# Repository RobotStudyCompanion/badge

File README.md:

# Tiny RSC Badge

This repository contains the PCB design files for the **Tiny RSC Badge**, developed for the Robotic Study Companion (RSC) project.

The board is a small electronic badge designed around an **astable multivibrator circuit** that drives blinking LEDs. The project was created as a simple and compact PCB badge for the RSC platform.

## Design Summary

The PCB was designed in **KiCad**.

The circuit is based on an astable multivibrator, where two transistor stages continuously switch between ON and OFF states, causing the LEDs to blink alternately.

The board includes:

- Astable multivibrator circuit
- Two LEDs
- Transistors
- Resistors and capacitors for controlling the oscillation
- Compact badge-style PCB layout

The design focuses on simplicity, low component count, and a compact form factor suitable for use as an electronic badge.

## PCB

### Front Side

### Back Side

## Final Product

The assembled Tiny RSC Badge:

---

## Author

Timur Kedrov and Matevž Borjan Zorec 

© Robot Study Companion 2026

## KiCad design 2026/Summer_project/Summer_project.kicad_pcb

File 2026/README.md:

# RSC Badge

This repository contains the PCB design files for the **RSC Badge**, developed for the Robot Study Companion (RSC; [rsc.ee](https://rsc.ee/)) project.

The board is a small electronic badge featuring an astable multivibrator circuit that drives blinking LEDs. 

For the circuit design we were explicitly inspired by the KiCad workshop at [https://gitlab.com/evils/kicad-workshop](https://gitlab.com/evils/kicad-workshop).

We prepared this project as a simple and compact PCB badge for RSC affiliated events.

## Design Summary

We designed the PCB in **KiCad 10.0**.

The astable multivibrator circuit comprises two transistor stages.

When pressing the button switch, the transistors alternate ON and OFF states, causing the LEDs to blink alternately, while the middle LED stays powered.

The board includes:
- Two LEDs
- Two transistors
- Button switch
- CR2032 battery holder
- Informative silkscreen
- Resistors and capacitors (current limiting and oscillation rate setting)
- Compact badge with a face-shape layout (pareidolia)

### Front

### Back

## Assembled 2026 RSC Badge:

---

## Author

Timur Kedrov and Matevž Borjan Zorec 

Supervised by Farnaz Baksh

© Robot Study Companion 2026

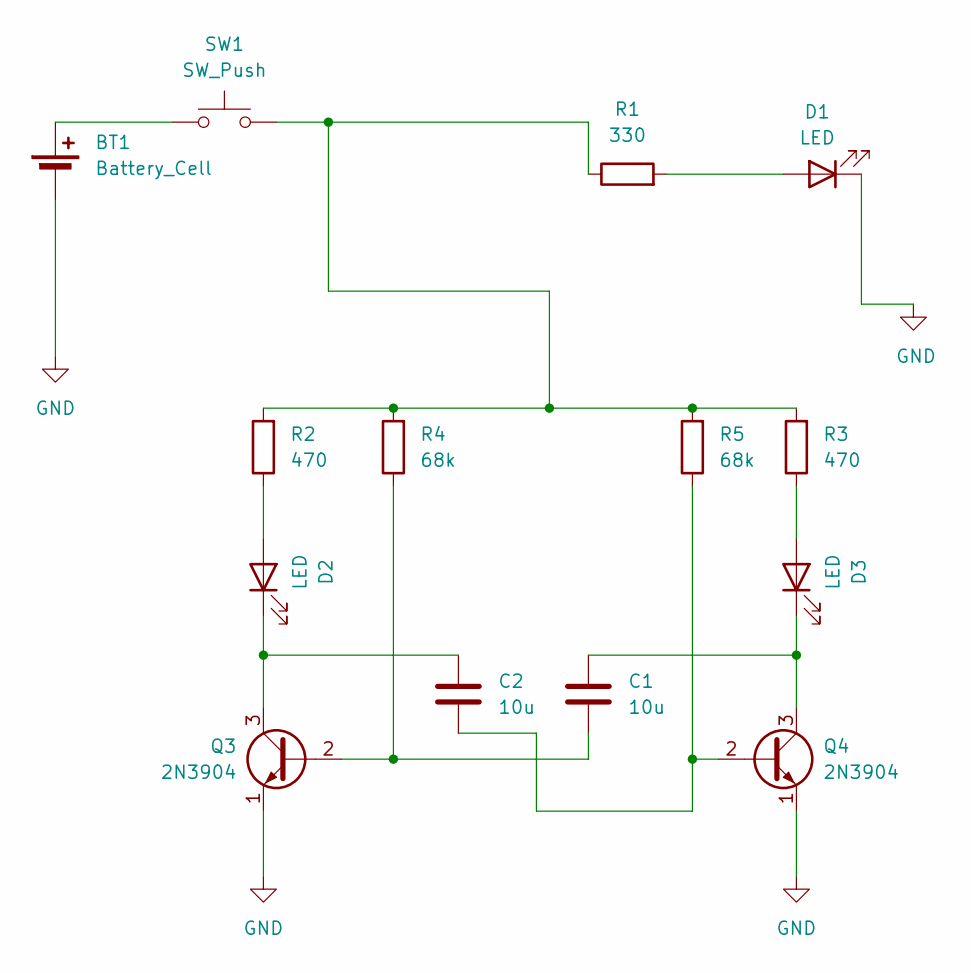
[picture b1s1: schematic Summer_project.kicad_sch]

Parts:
BT1: Battery_Cell; BAT_BAT-HLD-005-THM
C1, C2: 10u; CP_Radial_D5.0mm_P2.00mm
D1, D2, D3: LED; LED_D5.0mm
Q3, Q4: 2N3904; TO-92_Inline
R1: 330; R_Axial_DIN0207_L6.3mm_D2.5mm_P7.62mm_Horizontal
R2, R3: 470; R_Axial_DIN0207_L6.3mm_D2.5mm_P7.62mm_Horizontal
R4, R5: 68k; R_Axial_DIN0207_L6.3mm_D2.5mm_P7.62mm_Horizontal
SW1: SW_Push; SW_PUSH_6mm

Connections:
GND: BT1.2 (-), D1.1 (K), Q3.1 (E), Q4.1 (E)
unnamed: BT1.1 (+), SW1.1
unnamed: D1.2 (A), R1.2
unnamed: D2.2 (A), R2.1
unnamed: C2.1, D2.1 (K), Q3.3 (C)
unnamed: D3.2 (A), R3.1
unnamed: C1.1, D3.1 (K), Q4.3 (C)
unnamed: C1.2, Q3.2 (B), R4.1
unnamed: C2.2, Q4.2 (B), R5.1
unnamed: R1.1, R2.2, R3.2, R4.2, R5.2, SW1.2

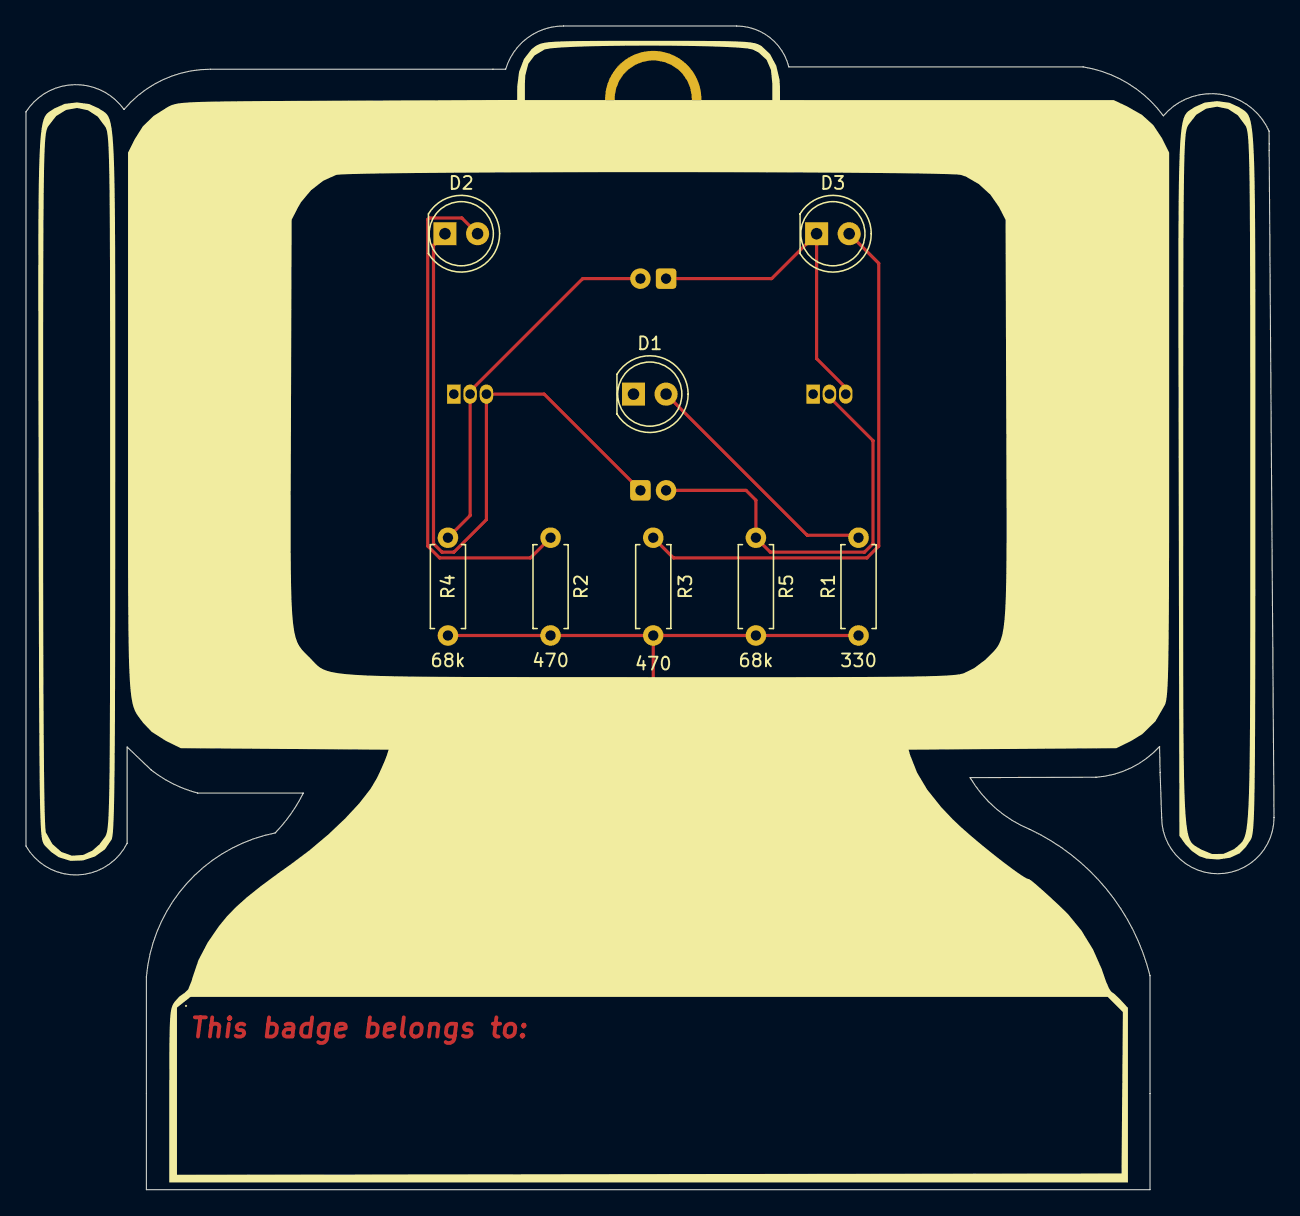
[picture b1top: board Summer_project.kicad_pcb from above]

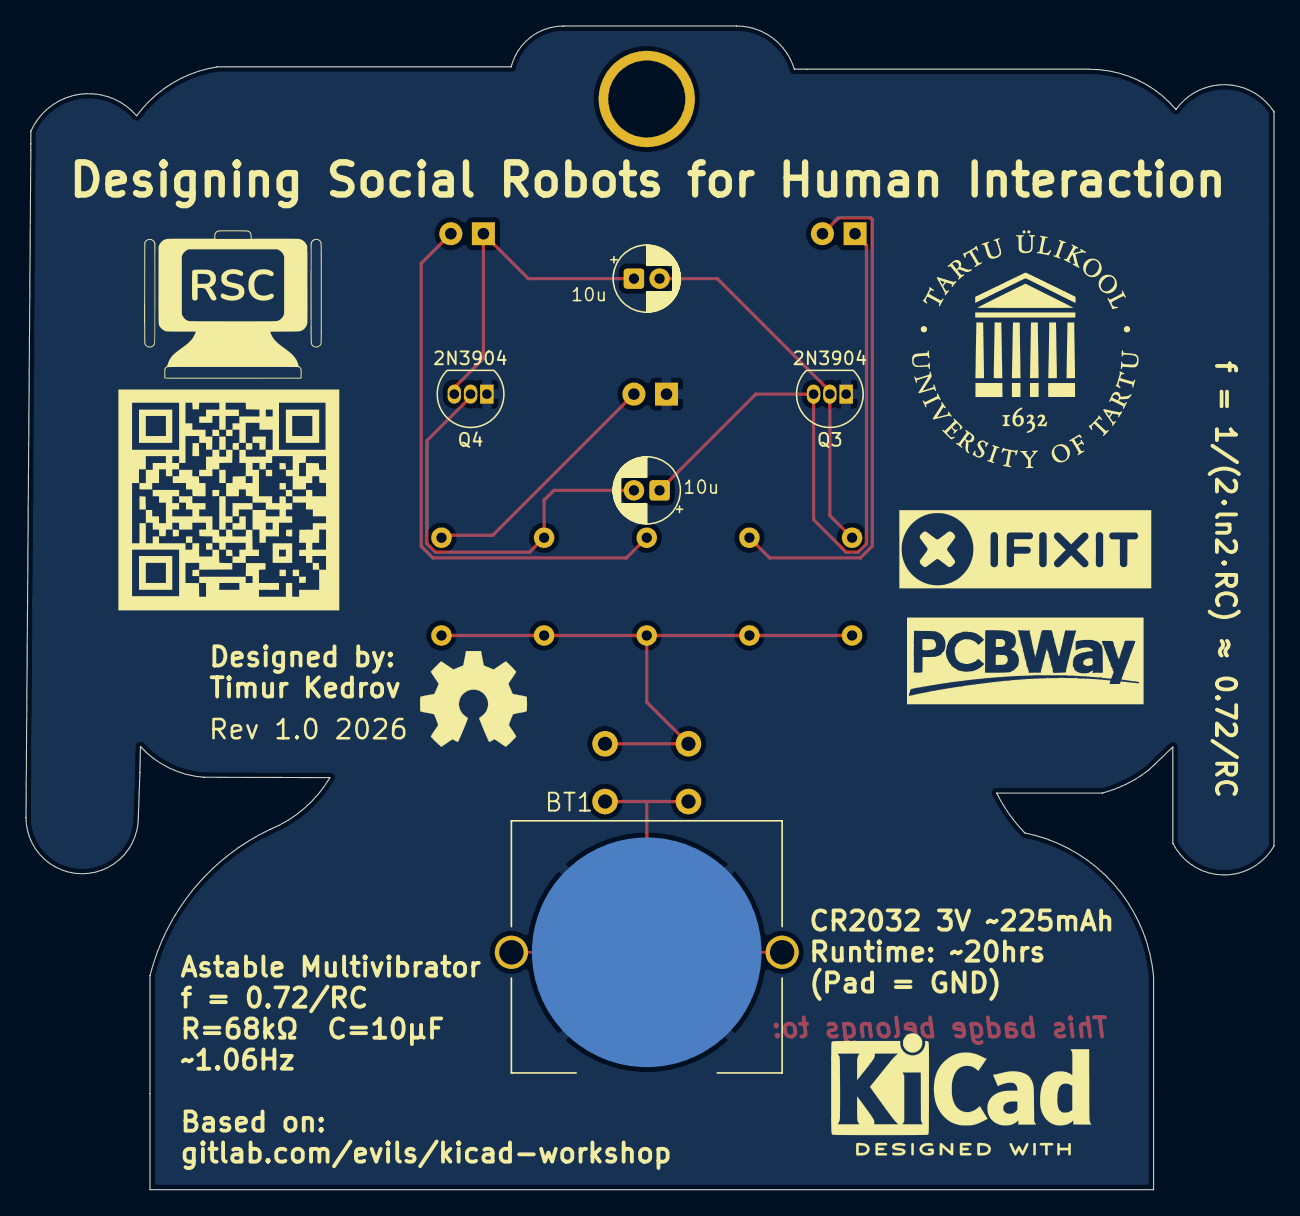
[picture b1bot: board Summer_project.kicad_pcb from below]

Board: 2 copper layers, 97.3 x 90.7 mm, 14 parts (5 on the bottom side), 10 nets.

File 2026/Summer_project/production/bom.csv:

Designator,Footprint,Quantity,Value,LCSC Part #
BT1,BAT_BAT-HLD-005-THM,1,Battery_Cell,
"C1, C2",CP_Radial_D5.0mm_P2.00mm,2,10u,
"D1, D2, D3",LED_D5.0mm,3,LED,
"Q3, Q4",TO-92_Inline,2,2N3904,
R1,R_Axial_DIN0207_L6.3mm_D2.5mm_P7.62mm_Horizontal,1,330,
"R2, R3",R_Axial_DIN0207_L6.3mm_D2.5mm_P7.62mm_Horizontal,2,470,
"R4, R5",R_Axial_DIN0207_L6.3mm_D2.5mm_P7.62mm_Horizontal,2,68k,
SW1,SW_PUSH_6mm,1,SW_Push,
